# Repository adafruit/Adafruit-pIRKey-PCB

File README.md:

## Adafruit pIRKey PCB

<a href="http://www.adafruit.com/products/3364"><br/>
Click here to purchase one from the Adafruit shop</a>

PCB files for the Adafruit pIRKey. Format is EagleCAD schematic and board layout

For more details, check out the product pages at
* https://www.adafruit.com/product/3364

### Description

The pIRkey adds an IR remote receiver to any computer, laptop, tablet...any computer or device with a USB port that can use a keyboard. This little board slides into any USB A port, and shows up as an every-day USB keyboard. The onboard ATSAMD21 microcontroller listens for IR remote signals and converts them to keypresses, mouse movements, or even USB serial output.

**Coming soon! We want to reprogram our stock with the newest CircuitPython version before shipping these out.**

Infrared is our favorite wireless protocol - no antennas, certifications, pairings, passwords, or special tools required. Works everywhere in the world and very intuitive - everyone's got an IR remote in their home!  Our original IRkey was a small USB-pluggable microcontroller board with an IR receiver, an Attiny85 microcontroller and indicator LED. When certain remote control commands were received, the IRkey would send corresponding keyboard presses. It was great, but was not easy to customize - you had to use the remote we sold it with.

The pIRkey is an improvement on our original IRkey product, by adding a p for python. Now that we have CircuitPython available for the tiny ATSAMD21E processor, we swapped it for the ATtiny85, giving a huge boost in power and a working Python interpreter on board as well. This means its super easy to reprogram, customize or adapt it to whatever Infrared-reading needs you may have.

When you plug it in, the pIRkey shows up as a triple device: USB disk drive to store code, USB serial for debugging and Python interactive command line, and USB keyboard/mouse that can transmit keypresses or mouse movements.

By default we ship with some very simple example code to read NEC remotes but you can use any remote that has about 38KHz output frequency which is the vast majority of remote controls. Here's some ideas: you could use pIRkey to remotely start/stop a program, shut down a computer, control a smart phone or tablet mounted far away, make adaptive controls, etc.

### License

Adafruit invests time and resources providing this open source design, please support Adafruit and open-source hardware by purchasing products from [Adafruit](https://www.adafruit.com)!

Designed by Limor Fried/Ladyada for Adafruit Industries.

Creative Commons Attribution/Share-Alike, all text above must be included in any redistribution. See license.txt for additional details.

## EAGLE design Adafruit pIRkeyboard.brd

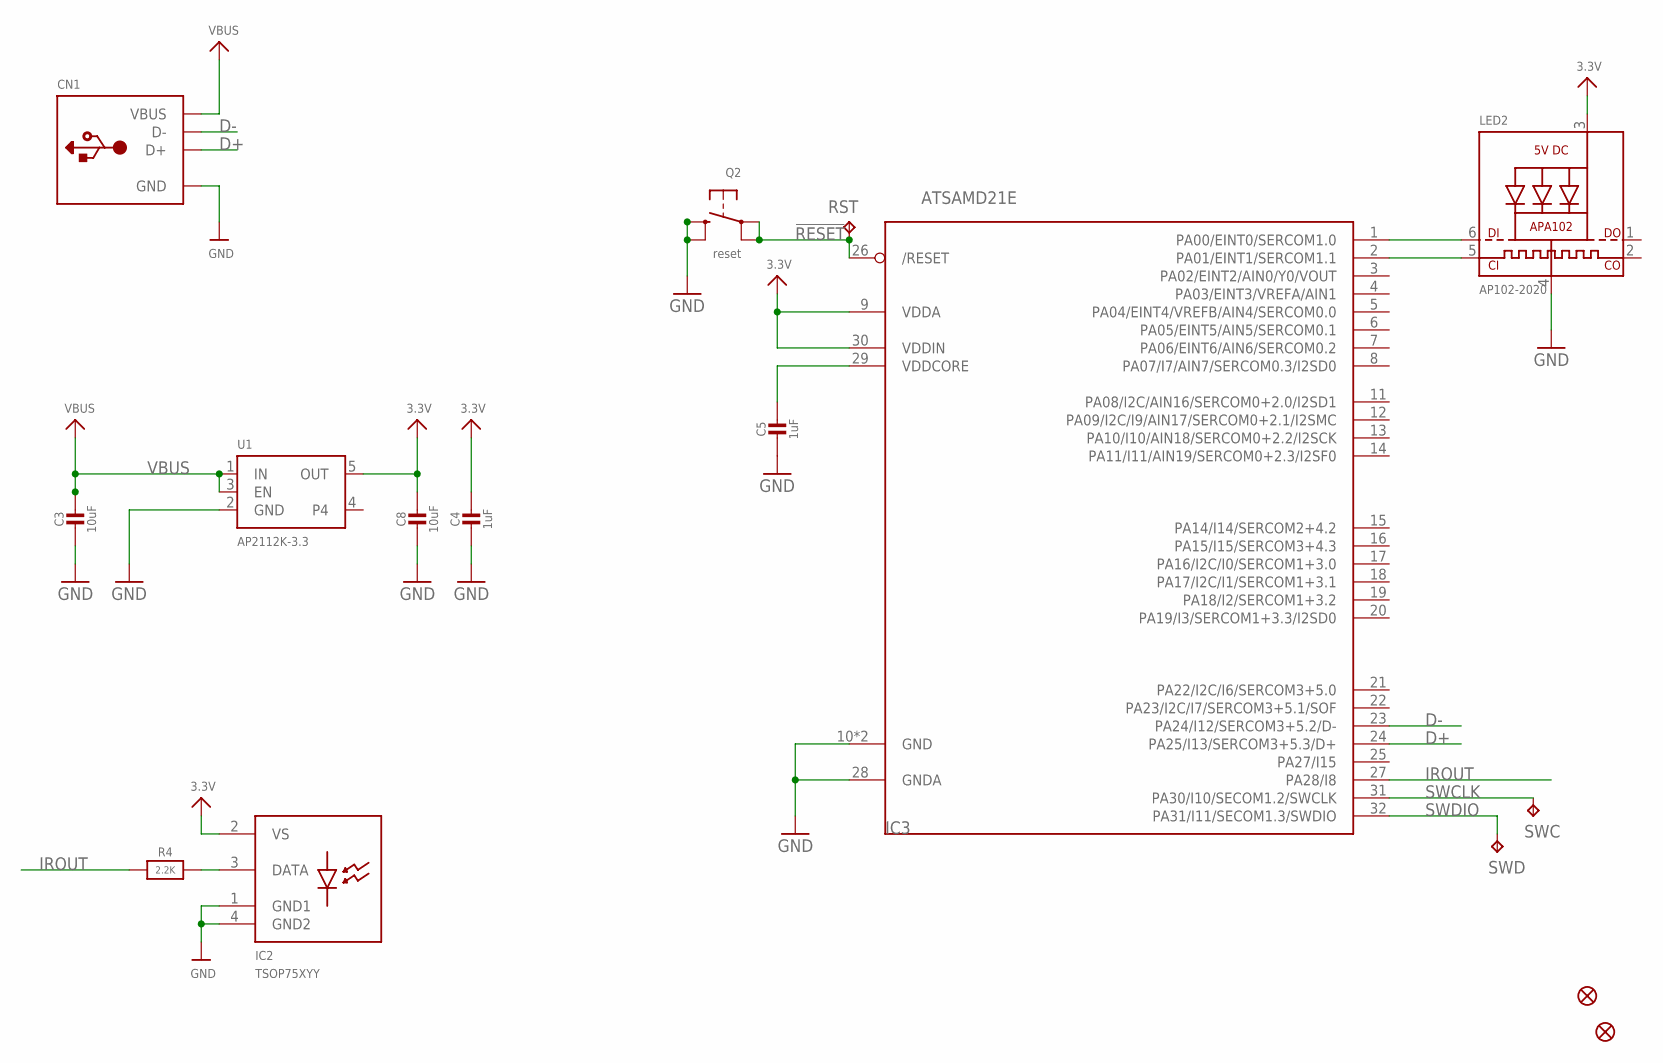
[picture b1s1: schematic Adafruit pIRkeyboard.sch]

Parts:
C3, C8: 10uF; 0805-NO
C4, C5: 1uF; 0603-NO
CN1: USB_TYPEAPCB; USBA_PCB
FID1, FID2: FIDUCIAL_1MM
IC2: TSOP75XYY
IC3: ATSAMD21E; QFN32_5MM
LED2: AP102-2020; APA102_2020
Q2: reset; BTN_KMR2_4.6X2.8
R4: 2.2K; 0603-NO
RST: TPTP16R; TP16R
SWC: TPTP15R; TP15R
SWD: TPTP16R; TP16R
U1: AP2112K-3.3; SOT23-5

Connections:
3.3V: C4.1, C8.1, IC2.2 (VS), IC3.9 (VDDA), IC3.30 (VDDIN), LED2.3 (VDD), U1.5 (OUT)
!RESET: IC3.26 (/RESET), Q2.A, Q2.A' (P1), RST.TP
A3: IC3.1 (PA00/EINT0/SERCOM1.0), LED2.6 (DI)
D+: CN1.USB_PLUS (D+), IC3.24 (PA25/I13/SERCOM3+5.3/D+)
D-: CN1.USB_NEG (D-), IC3.23 (PA24/I12/SERCOM3+5.2/D-)
GND: C3.2, C4.2, C5.2, C8.2, CN1.GND, IC2.1 (GND1), IC2.4 (GND2), IC3.10 (GND), IC3.28 (GNDA), IC3.33 (GND), LED2.4 (GND), Q2.B (S), Q2.B' (S1), U1.2 (GND)
IROUT: IC3.27 (PA28/I8), R4.1
unnamed: IC2.3 (DATA), R4.2
unnamed: IC3.2 (PA01/EINT1/SERCOM1.1), LED2.5 (CKI)
SWCLK: IC3.31 (PA30/I10/SECOM1.2/SWCLK), SWC.TP
SWDIO: IC3.32 (PA31/I11/SECOM1.3/SWDIO), SWD.TP
VBUS: C3.1, CN1.VCC (VBUS), U1.1 (IN), U1.3 (EN)
VDDCORE1: C5.1, IC3.29 (VDDCORE)

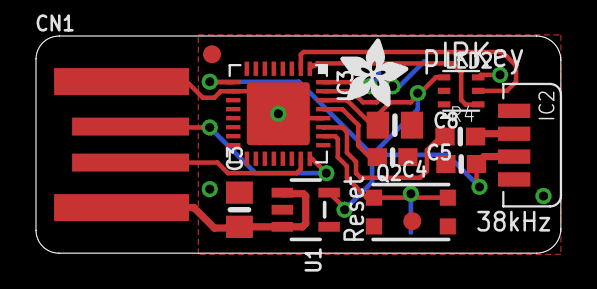
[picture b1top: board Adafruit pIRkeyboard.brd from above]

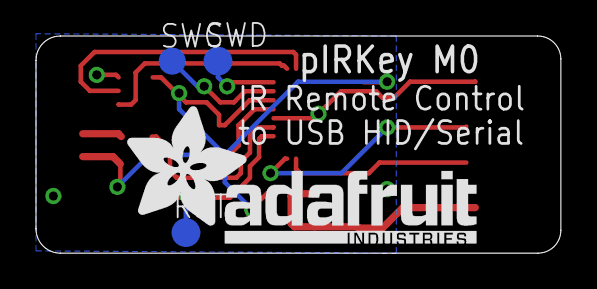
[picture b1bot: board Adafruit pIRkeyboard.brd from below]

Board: 2 copper layers, 29.2 x 12.1 mm, 18 parts (4 on the bottom side), 13 nets.

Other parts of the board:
U$8: ADAFRUIT_TEXT_20MM
U$12: ADAFRUIT_3.5MM

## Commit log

2018-05-23 init

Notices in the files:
parts and their libraries:
microbuilder: This work is placed in the public domain, and may be freely used for commercial and non-commercial work with the following conditions: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
